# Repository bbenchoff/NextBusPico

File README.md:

# Multi-Stop Bus Tracker (and a tide display. and possibly weather.)

I live in SF, with some of the best public transit in the country. I would like to know when the next bus will be arriving at a stop near my house. Not just one stop, either: there are several bus lines that will all take me downtown, but they're all served by different stops. I need a device that will ping the city's API for _all_ the bus stops near my house, and condense that into a list I can put on a small display somewhere. I don't want to dedicate a whole computer to this task, so I need to build an embedded solution.

This is somewhat different than the displays actually found at bus stops around the city (above). By their nature, the displays at one bus stop do not track the arrivals at other nearby bus stops. It can be done, I just need the data. This can be done through the [511.org API](https://511.org/). Given any bus stop in the city, this API will give me predicted times of arrivals each bus scheduled at that stop, its line number/letter, and its destination. There is a rate limit on this API of 60 requests per hour, but that only means I'm sending a request every 65 seconds.

But there are a few problems:

- The 511.org API *only* works with HTTPS. 
- The API *only* gives me gzipped JSON. I need to decompress this on the device.
- I need to do this on an embedded device. I'm using a Pi Pico2W, simply because that's the bullshit I'm currently on.

## Previous work and initial steps

I started this project with just a Raspberry Pi Pico (with Ethernet) simply as a proof of concept that it's possible to pull arrival data in an embedded device. [Some reddit user](https://www.reddit.com/r/sanfrancisco/comments/16x7zi4/made_a_next_muni_timer_with_a_few_other_handy/) built something similar with an ESP-32, but was confounded by the fact that 511.org only works with HTTPS, and the API only returns gzipped JSON. The solution for that project was to build a Node app to download and decompress the data. This is not an ideal solution.

There is [another project that does something like this](https://github.com/mmichon/esp-nextbus-mini/tree/master), using an ESP-8266. This project does not ping the 511.org API directly, but simply downloads data from [nextbus](http://nextbus.com/). Again, the two key problems are not addressed. This uses a second server, and doesn't interact with the 'ground truth' of the actual API data. Also the display on both of the above devices is really small.

The ideal solution should work even if there are only two computers left on the planet -- the 511.org server, and this device. This means solving the problems of getting data over HTTPS and decompressing the JSON file. I should also use a _good_ display for this, because I really hate how small those little I₂C displays are.

To solve these problems, I picked up a Pi Pico board with an Ethernet module tacked on. In my real job I've found this to be a great way to get data off a network, and the Pico should have more than enough RAM to store the decompressed JSON as well as a screenbuffer or two. The Pico with Ethernet board allowed me to move over to a PicoW board in the future, giving me WiFi connectivity. 

## Problem 1: HTTPS and Decompressing JSON

Getting data from the 511.org API presents two immediate challenges: the API requires HTTPS connections, and it only returns gzipped JSON data. This is an unusual requirement for embedded projects; most examples of accessing web APIs on microcontrollers use plain HTTP, and compressed data is rarely seen in embedded applications.

HTTPS was the easier of these problems to solve; the SSLClient library for Arduino handles the SSL/TLS handshake and encryption. The only tricky part was getting the correct SSL certificates in the right format. [A web-based tool](https://openslab-osu.github.io/bearssl-certificate-utility/) creates a trust_anchors.h file containing the certificates needed for SSL verification - you just input the domain name (api.511.org) and it generates the properly formatted certificate array that SSLClient needs. With the correct certificates in place, SSLClient manages the encrypted connection transparently.

Figuring out the payload was another matter entirely. At first, every response I was getting from the server was garbage, even when telling the server to send me *un*compressed JSON. Looking at the hex dump of the data I was receiving told me another story.

### I can not tell you how many times looking at a hex dump has saved my ass.

The 0x1F 0x8B is the magic number for gzip encoding. Once I saw that, I knew I needed a library for decompressing gzip on an embedded platform. I found the [miniz library](https://github.com/richgel999/miniz), a portable library in C that handles the decompression. Even with this library, it's tricky; I need to skip past the 10-byte header, extract the uncompressed size from the last 4 bytes, and decompress everything in between. I also need to manage the memory correctly with malloc() and free(), and no I haven't learned Rust yet. 

## Problem 2: Organizing this data

The 511.org API gives me a lot of data for each bus stop - route numbers, destinations, arrival times, and current locations. But I need to track multiple stops at once, and merge all this information into something useful. This meant creating a data structure that could handle multiple stops and multiple arrivals at each stop.

The solution I came up with uses a simple array of stop data structures. Each stop structure contains its stop code (a unique identifier for each bus stop) and an array of upcoming arrivals. Each arrival contains the bus line number, destination, arrival time, and stop name. The size of these arrays is fixed - I can track up to 20 arrivals per stop, which is more than enough for my needs.

When new data comes in from the API, I clear out the old arrivals for that stop and fill in the new ones. There's also a cleanup function that removes arrivals that have already passed. The most interesting part is how the display function handles all this data - it looks through all stops and all arrivals, groups buses going to the same destination, and creates a consolidated list of arrival times. For example, if the 48 bus is coming to the same stop in 5, 20, and 35 minutes, it shows up as one line: "48 Inbound in 5, 20, 35 minutes". Pinging two stops means I can also get "28 to the Presidio in 2, 12, 23 minutes".

The above is the device pinging four bus stops ({"15696", "15565", "13220", "15678"}) around Market and Van Ness. Each stop has several bus lines on it, and the code correctly displays the line, destination, and arrival time. This might seem like overkill for just checking bus times, but it means I can glance at the display and immediately see every bus that's coming to any stop near my house, sorted by arrival time.

## Problem 3: Let's add a display!

This thing needs a display, something low power, too. I settled on an ePaper display, the [Microtips MT-DEPG0750RWU790F30](https://www.mouser.com/ProductDetail/Microtips-Technology/MT-DEPG0750RWU790F30?qs=Y0Uzf4wQF3nnUJiBp%2FvOzg%3D%3D), a 7.5" display with a resolution of 480x800. There are a few things that brought me to this display: it has an on-chip framebuffer, which can [vastly increase capabilities if you're smart](https://bbenchoff.github.io/pages/dumb.html), and programmable waveforms for the eInk. This is a display meant for price labels in a grocery store, so the refresh rate isn't great.

I whipped up a board in KiCad that would support this board. The panel driver circuit is ripped straight from the datasheet and drives the panel with SPI. In addition to that, I added a few [solderable standoffs](https://www.digikey.com/en/products/detail/w%C3%BCrth-elektronik/9774060360R/4810237) and a power circuit built around TI's TPS560200, giving me 3.3V from 4.5V to 17V. There is a vertical USB-C (power only) on the board, because i envision this being something like a picture frame. There is also a ~12VDC power input ORed with the USB-C power input in case I ever want to install this inside a wall.

Writing the driver/library for the e-paper display proceeded as it usually does when I write a display driver -- tearing my hair out and somehow it magically works.

## E-Paper display pain points

This is not instructions on how to write a driver for an e-paper display. Instead, this is a log of what I found difficult. If you just want the code, it's somewhere over [in the github repo for this project](https://github.com/bbenchoff/nextBusPico).

### Pain Points and Displaying Images

This code uses a small subset of the [Adafruit GFX library](https://github.com/adafruit/Adafruit-GFX-Library) for housekeeping tasks such as rotation and loading a set image format into RAM. This also gives me a stock font so error messages can be displayed on the screen. However, the actual display needs a much more robust and aesthetically pleasing solution.

While standard bitmap fonts are good enough for the text, the bus routes themselves needed something _extra_. I created about seventy 180x180 pixel graphics for **all** of the bus and transit routes in SF. The design is Bahnschrift Bold, 175pt for the main letter/number, 24pt of supplementary text. Rail lines are in giant circles, cable cars are cute little cable cars, and the 39 Coit is Coit tower. I'm not happy with all of the route logos, but it's a start:

I had a few pain points in developing this code, the first being what happens every time I write a display driver. Because I'm using this in a portrait orientation, the display was all cattywampus -- up was right, left was down, and at one point the display was mirrored in the vertical axis. This is a pain, but I just had to work through it.

The second pain point was the lack of a partial refresh for the display. The core function of this display means it doesn't change much. It's just a list of bus lines, their destinations, a stop point, and a list of minutes until the bus arrives. Obviously the arrival time changes every 60 seconds, but the rest of the display will usually only change late at night when the busses stop running or early in the morning. A partial refresh for just the arrival times is the way to go.

Unfortunately, the display I'm using for this project doesn't support partial refresh. I thought it did -- why wouldn't an e-paper display support partial refresh? The MT-DEPG0750RWU790F30 does not, however. But pinouts for 7.5" e-paper displays are all very similar, and I can use the same breakout board to test out other panels.

## An enclosure

The enclosure is a 3-piece ordeal. The legs bolt onto the back with heat-set inserts installed in the back. The PCB/EPD assembly mounts to the back of the display with the solderable standoffs installed on the PCB. The front is a snap-fit assembly, with the geometry shown in the sectional diagram below.

These parts were 3D printed on a Prusa Mk4 in carbon fiber-filled PC. I'm only building one of these, after all.

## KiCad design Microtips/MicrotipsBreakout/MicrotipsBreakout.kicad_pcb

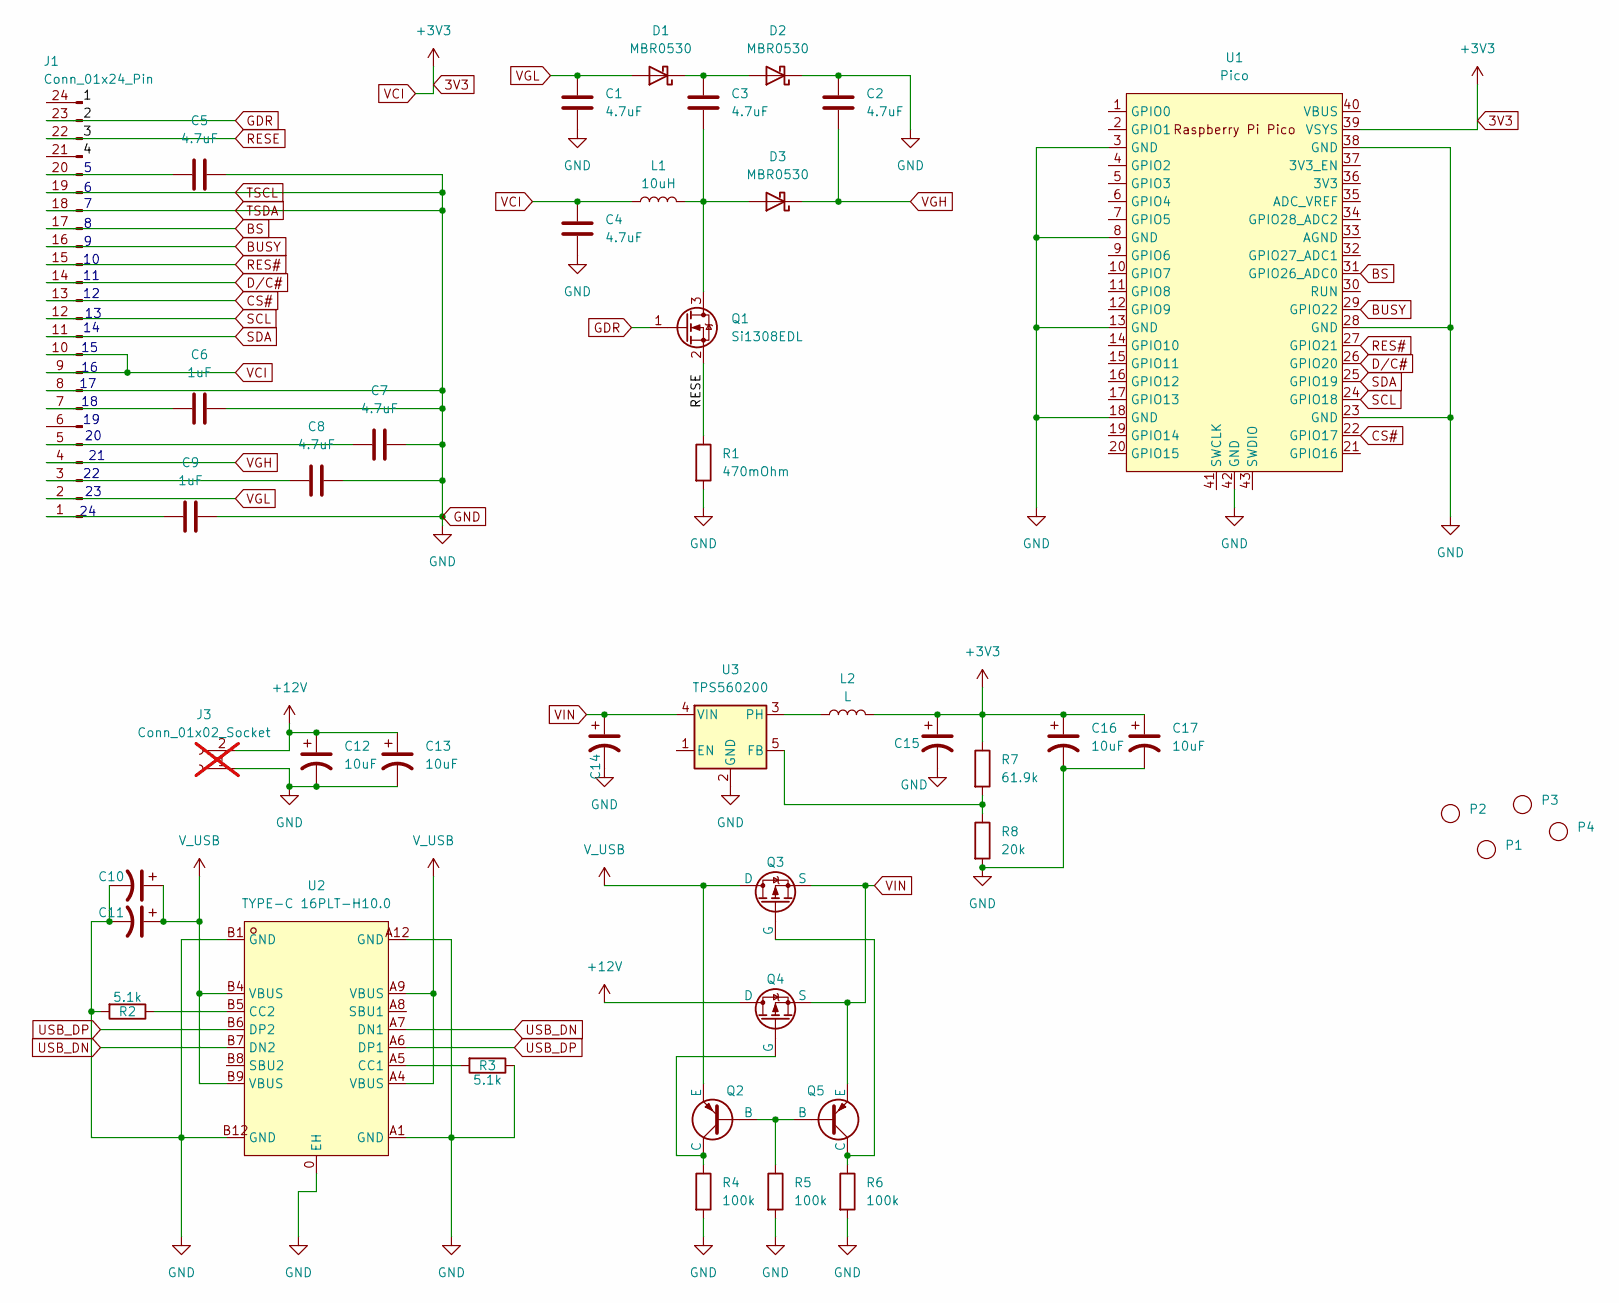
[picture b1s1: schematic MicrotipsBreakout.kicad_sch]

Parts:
C1, C2, C3, C4, C5, C7, C8: 4.7uF; C_1206_3216Metric; LCSC Part C132148
C6, C9: 1uF; C_1206_3216Metric; LCSC Part C28322
C10, C11, C12, C13, C16, C17: 10uF; CP_EIA-3528-12_Kemet-T; LCSC Part C7193
C14, C15: 10uF; C_1206_3216Metric; LCSC Part C14860
D1, D2, D3: MBR0530; D_SOD-123; LCSC Part C41383968
J1: Conn_01x24_Pin; Jushuo_AFC07-S24FCA-00_1x24-1MP_P0.50_Horizontal
J3: Conn_01x02_Socket; PinSocket_1x02_P2.54mm_Vertical; not fitted
L1: 10uH; L_TDK_VLS6045EX_VLS6045AF; LCSC Part C360734
L2: L; L_Chilisin_BMRB00050518-B; LCSC C5349679
P1, P2, P3, P4: 9774060360R
Q1: Si1308EDL; SOT-323_SC-70; LCSC Part C7603347
Q2, Q5: PNP; SOT-23; LCSC C5300004
Q3, Q4: PMOS; SOT-23; LCSC C347476
R1: 470mOhm; R_0805_2012Metric; LCSC Part C705493
R2, R3: 5.1k; R_0603_1608Metric; LCSC C23186
R4, R5, R6: 100k; R_0603_1608Metric; LCSC C2906980
R7: 61.9k; R_0603_1608Metric; LCSC C23091
R8: 20k; R_0603_1608Metric; LCSC C4184
U1: Pico; RPi_Pico_SMD_TH
U2: TYPE-C 16PLT-H10.0; TYPE-C-SMD_USB4120-03-C; LCSC Part C3151749
U3: TPS560200; SOT-23-5; LCSC C83671

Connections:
3V3: C4.1, C15.1, C16.1, C17.1, J1.9, J1.10, L1.1, L2.2, R7.1, U1.39 (VSYS)
+12V: C12.1, C13.1, J3.2, Q4.3 (D)
BS: J1.17, U1.31 (GPIO26_ADC0)
BUSY: J1.16, U1.29 (GPIO22)
CS#: J1.13, U1.22 (GPIO17)
D/C#: J1.14, U1.26 (GPIO20)
GDR: J1.23, Q1.1 (G)
GND: C1.2, C2.1, C4.2, C5.2, C6.2, C7.2, C8.2, C9.2, C10.2, C11.2, C12.2, C13.2, C14.2, C15.2, C16.2, C17.2, D2.1 (K), J1.8, J1.18, J1.19, J3.1, R1.2, R2.2, R3.1, R4.2, R5.2, R6.2, R8.2, U1.3 (GND), U1.8 (GND), U1.13 (GND), U1.18 (GND), U1.23 (GND), U1.28 (GND), U1.38 (GND), U1.42 (GND), U2.0 (EH), U2.A1 (GND), U2.A12 (GND), U2.B1 (GND), U2.B12 (GND), U3.2 (GND)
unnamed: C3.1, D1.1 (K), D2.2 (A)
unnamed: C3.2, D3.2 (A), L1.2, Q1.3 (D)
unnamed: C9.1, J1.1
unnamed: C8.1, J1.3
unnamed: C7.1, J1.5
unnamed: C6.1, J1.7
unnamed: C5.1, J1.20
unnamed: Q2.1 (B), Q5.1 (B), R5.1
unnamed: Q2.3 (C), Q4.1 (G), R4.1
unnamed: Q3.1 (G), Q5.3 (C), R6.1
unnamed: R3.2, U2.A5 (CC1)
unnamed: R2.1, U2.B5 (CC2)
unnamed: R7.2, R8.1, U3.5 (FB)
unnamed: L2.1, U3.3 (PH)
RES#: J1.15, U1.27 (GPIO21)
RESE: J1.22, Q1.2 (S), R1.1
SCL: J1.12, U1.24 (GPIO18)
SDA: J1.11, U1.25 (GPIO19)
USB_DN: U2.A7 (DN1), U2.B7 (DN2)
USB_DP: U2.A6 (DP1), U2.B6 (DP2)
VGH: C2.2, D3.1 (K), J1.4
VGL: C1.1, D1.2 (A), J1.2
VIN: C14.1, Q3.2 (S), Q4.2 (S), Q5.2 (E), U3.4 (VIN)
V_USB: C10.1, C11.1, Q2.2 (E), Q3.3 (D), U2.A4 (VBUS), U2.A9 (VBUS), U2.B4 (VBUS), U2.B9 (VBUS)

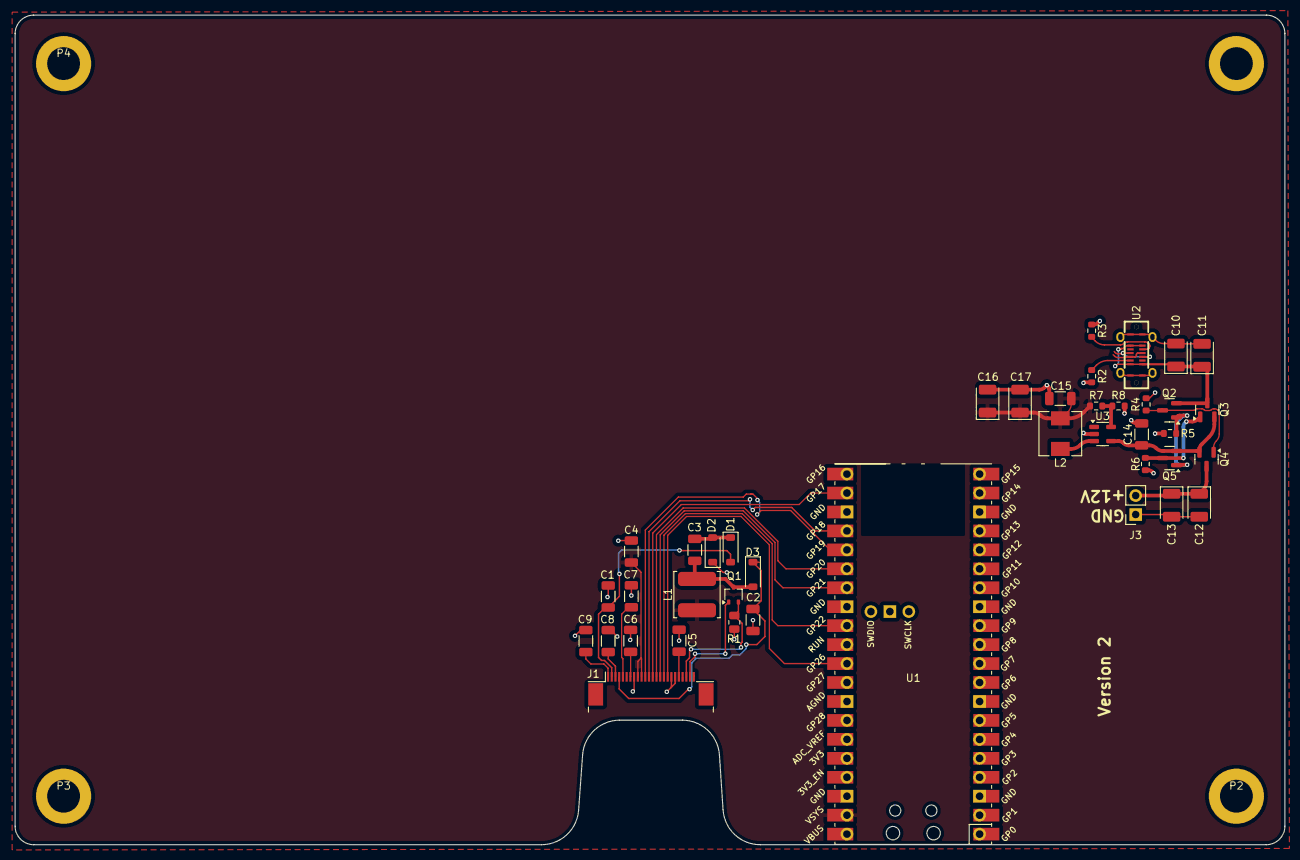
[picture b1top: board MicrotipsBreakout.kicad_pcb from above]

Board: 2 copper layers, 170.2 x 111.2 mm, 44 parts (0 on the bottom side), 32 nets.

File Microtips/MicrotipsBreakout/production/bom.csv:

Designator,Footprint,Quantity,Value,LCSC Part #
"C1, C2, C3, C4, C5, C7, C8",1206,7,4.7uF,
"C10, C11, C12, C13, C16, C17",CP_EIA-3528-12_Kemet-T,6,10uF,
"C14, C15",1206,2,10uF,
"C6, C9",1206,2,1uF,
"D1, D2, D3",D_SOD-123,3,MBR0530,
J1,Jushuo_AFC07-S24FCA-00_1x24-1MP_P0.50_Horizontal,1,Conn_01x24_Pin,
L1,L_TDK_VLS6045EX_VLS6045AF,1,10uH,
L2,L_Chilisin_BMRB00050518-B,1,L, C5349679
"P1, P2, P3, P4",9774060360R,4,~,
Q1,SOT-323_SC-70,1,Si1308EDL,
"Q2, Q5",SOT-23,2,PNP, C5300004
"Q3, Q4",SOT-23,2,PMOS, C347476
R1,0805,1,470mOhm,
"R2, R3",0603,2,5.1k,C23186
"R4, R5, R6",0603,3,100k,C2906980
R7,0603,1,61.9k,C23091
R8,0603,1,20k,C4184
U1,RPi_Pico_SMD_TH,1,Pico,
U2,TYPE-C-SMD_USB4120-03-C,1,TYPE-C 16PLT-H10.0,
U3,SOT-23-5,1,TPS560200,C83671

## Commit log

2024-02-02 adding arduino hardware
2024-02-02 getting data but gzipped
2024-02-03 wtf why can't I un-gzip
2024-02-04 Everything working, now clean it up
2024-02-05 Getting the time and correctly parsing the json strings
2024-02-05 now has 'minutes until'
2024-02-06 slight refactor
2024-02-08 Figured out the thing
2024-02-09 trying json again
2024-02-12 The fuckin thing works now
2024-02-13 Significantly organize this shit
2024-02-22 pico update
2024-02-24 change SPI implementation
2025-01-22 Start on the microtips PCB
2025-01-23 Added Pico
2025-02-12 made graphics; building EPD driver
2025-02-14 trying some new shit
2025-02-14 stuff
2025-02-14 Lotta stuff changed
2025-02-14 small update
2025-02-24 basic test, this can write red white and black to the display
2025-02-25 Stuff works
2025-02-25 trying to get partial updates working
2025-02-25 I have no idea, we're changing over to another panel
2025-02-26 Save stuff here, build from here
2025-02-26 Added stuff, I think it might be done
2025-03-10 move stuff around, make gitignore
2025-09-22 save
2026-06-20 Bulletproofed the thing -- no longer stalls, WTD
